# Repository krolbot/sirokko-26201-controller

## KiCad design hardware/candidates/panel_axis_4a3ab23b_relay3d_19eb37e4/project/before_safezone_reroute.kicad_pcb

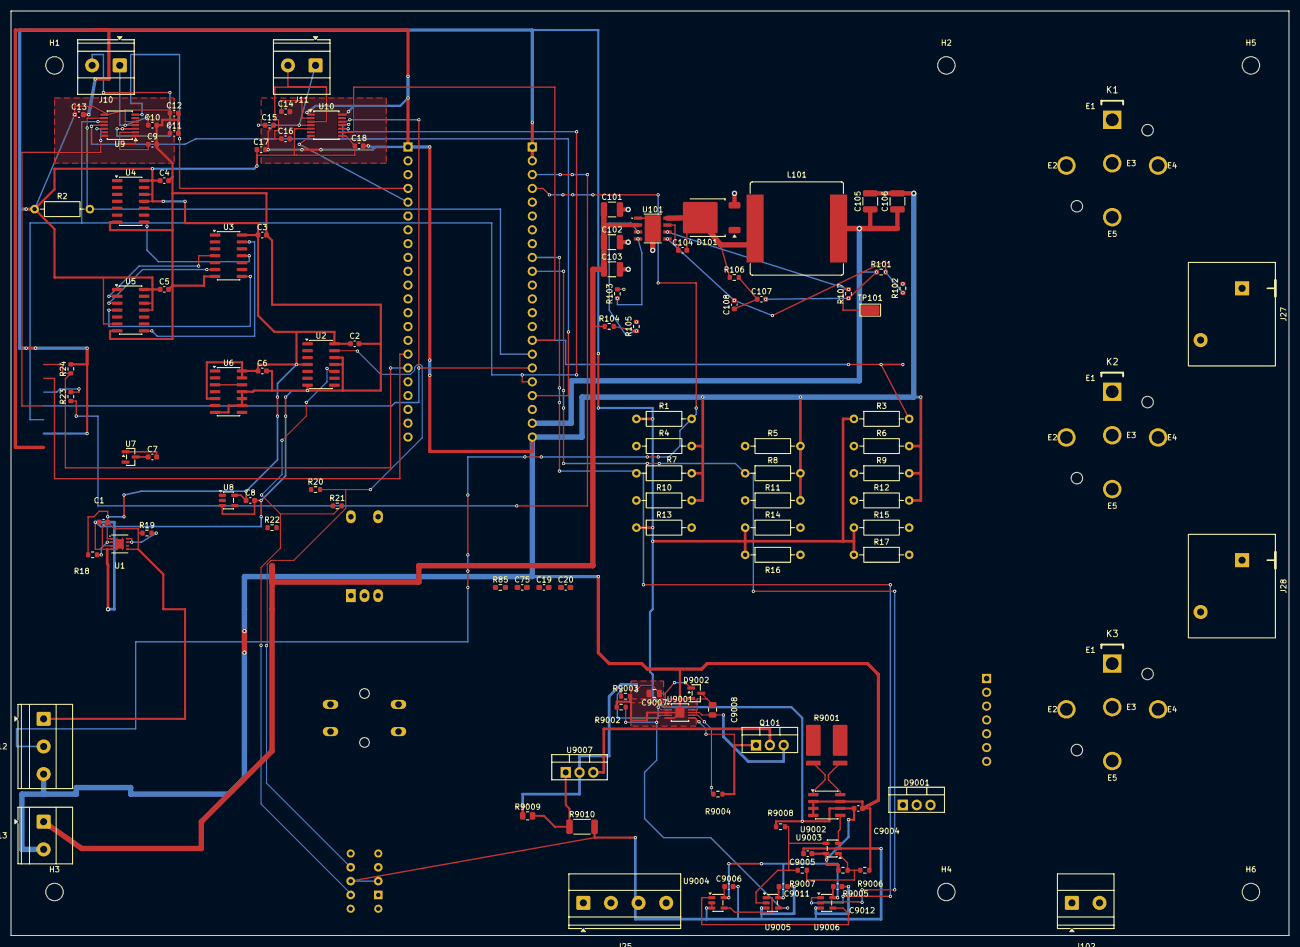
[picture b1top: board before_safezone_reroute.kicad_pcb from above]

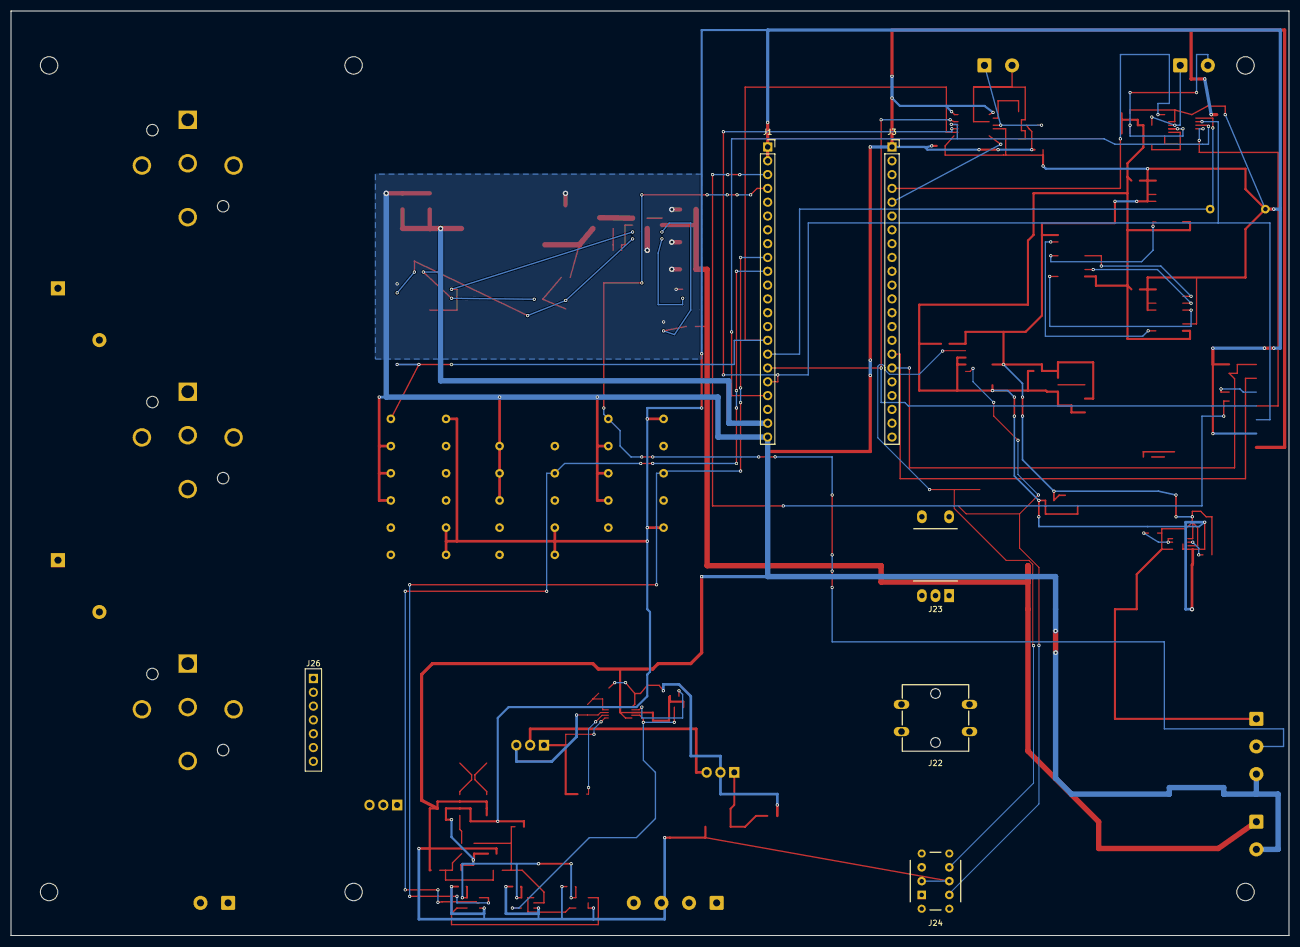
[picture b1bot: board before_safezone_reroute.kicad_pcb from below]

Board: 2 copper layers, 235.0 x 170.0 mm, 125 parts (6 on the bottom side), 76 nets.

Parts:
C1, C2, C3, C4, C5, C6, C7, C8: 100n 16V X7R; C_0603_1608Metric
C9, C14: 0.1uF X7R 16V BIAS; C_0603_1608Metric
C10, C15: 0.01uF X7R 16V T+ filter; C_0603_1608Metric
C11, C16: 0.01uF X7R 16V T- filter; C_0603_1608Metric
C12, C17: 0.1uF X7R 16V AVDD; C_0603_1608Metric
C13, C18: 0.1uF X7R 16V DVDD; C_0603_1608Metric
C19: 10n ENC_A_FILTER; C_0603_1608Metric_Pad1.08x0.95mm_HandSolder
C20: 10n ENC_B_FILTER; C_0603_1608Metric_Pad1.08x0.95mm_HandSolder
C75: 10n; C_0603_1608Metric_Pad1.08x0.95mm_HandSolder
C101, C102: 2.2uF 100V X7R; C_1210_3225Metric
C103: 22uF 100V BULK; C_1210_3225Metric
C104: 2.2nF 50V X7R; C_0603_1608Metric
C105, C106: 47uF 16V X7R; C_1210_3225Metric
C107: 4.7nF 50V C0G; C_0603_1608Metric
C108: 820pF 50V C0G; C_0603_1608Metric
C9004, C9005, C9006: 100nF X7R 16V; C_0603_1608Metric
C9007: 1uF ±10% X7R 50V 0805; LTC7001 VCC local decoupli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; C_0805_2012Metric
C9008: 1uF ±10% X7R 50V 0805 (BST-TS); C_0805_2012Metric
C9011: 100nF X7R 16V 10%; U9005 local bypass; C_0603_1608Metric
C9012: 100nF X7R 16V 10%; U9006 local bypass; C_0603_1608Metric
D101: STPS5H100B-TR; TO-252-2
D9001: STPS30H100CW; common cathode: K/pin2/tab -> MOTOR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; TO-220-3_Vertical
D9002: MMBD1501A; 200V 200mA silicon low-leakage bootstr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; SOT-23
H1, H2, H3, H4: M3; MountingHole_3.2mm_M3
H5, H6: M3 SUPPORT; MountingHole_3.2mm_M3
J1: DEVKITC1_J1; PinSocket_1x22_P2.54mm_Vertical
J3: DEVKITC1_J3; PinSocket_1x22_P2.54mm_Vertical
J10: TC_K_EXHAUST_T+_T-; TerminalBlock_Phoenix_MKDS-1,5-2-5.08_1x02_P5.08mm_Horizont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
J11: TC_K_AIR_T+_T-; TerminalBlock_Phoenix_MKDS-1,5-2-5.08_1x02_P5.08mm_Horizont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
J12: ROOM_DS18B20_HARNESS; TerminalBlock_Phoenix_MKDS-1,5-3-5.08_1x03_P5.08mm_Horizont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
J13: 24V_LOGIC_INPUT_ONLY__DRAFT_NOT_FOR_ORDER; TerminalBlock_Phoenix_MKDS-1,5-2-5.08_1x02_P5.08mm_Horizont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
J22: START_STOP B3F-4055 + B32-1380 RED; SW_SPST_Omron_B3F-40xx
J23: ENCODER EC11E15244G1; RotaryEncoder_Alps_EC11E15244G1
J24: RESET NKK BB25AB-FA; SW_NKK_BB25AB-FA
J25: THERMAL_AND_HW_ENABLE_3V3_ONLY; TerminalBlock_Phoenix_MKDS-1,5-4-5.08_1x04_P5.08mm_Horizont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
J26: TFT_GMT020-02-7P_ST7789V_7P_SOCKET__FOOTPRINT_NOT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; Connfly_DS1023_1x07S21_P2.54mm
J27: GLOW_OUTPUT_PHOENIX_1756993__POWER_PATH_NOT_CONNE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; Phoenix_1756993_MKDS5HV_2_9.52_ZSZS
J28: CLUTCH_OUTPUT_PHOENIX_1756993__POWER_PATH_NOT_CON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; Phoenix_1756993_MKDS5HV_2_9.52_ZSZS
J102: MOTOR_24V_HIGH_SPEED; 125W_HEATER_NAMEPLATE_NOT_M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; TerminalBlock_Phoenix_MKDS-1,5-2-5.08_1x02_P5.08mm_Horizont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
K1, K2, K3: DZ85AB-5-PCB MECH HOLD; DZ85AB_5_PCB_MECHANICAL_PINMAP_HOLD
L101: 33uH Isat>=10A; L_Bourns_SRP1770TA_16.9x16.9mm
Q101: IRFB4110PBF (100V; RDS(on) @ VGS=10V); TO-220-3_Vertical
R1: 4k7; R_Axial_DIN0207_L6.3mm_D2.5mm_P10.16mm_Horizontal
R2, R3, R4, R5, R6, R7, R8, R9, R10, R11, R12, R13, R14, R15: 10k; R_Axial_DIN0207_L6.3mm_D2.5mm_P10.16mm_Horizontal
R16: 2.2k ENC_A_PULLUP; R_Axial_DIN0207_L6.3mm_D2.5mm_P10.16mm_Horizontal
R17: 2.2k ENC_B_PULLUP; R_Axial_DIN0207_L6.3mm_D2.5mm_P10.16mm_Horizontal
R18, R19, R20, R21, R22, R102, R105, R107: 10k 1%; R_0603_1608Metric
R23: 33R TFT_RESET_SERIES; R_0603_1608Metric
R24: 10k TFT_CS_PULLUP; R_0603_1608Metric
R85: 2.2k; R_0603_1608Metric_Pad0.98x0.95mm_HandSolder
R101, R103: 31.6k 1%; R_0603_1608Metric
R104: 100k 1%; R_0603_1608Metric
R106: 82k 1%; R_0603_1608Metric
R9001: WSLP27262L000FEA; 2mOhm 1% 5W @70C; WSLP2726
R9002: 100k 1% gate-command pull-down; R_0603_1608Metric
R9003: 130k 1% (VCCUV ≈9.1V rising); R_0603_1608Metric
R9004: 10R gate turn-on damping; R_0603_1608Metric
R9005: 30.1k 1% OCP threshold high; R_0603_1608Metric
R9006: 10.0k 1% OCP threshold low; R_0603_1608Metric
R9007: 1.00M 1% OCP hysteresis feedback; R_0603_1608Metric
R9008: 10k 1% OCP_OK pull-up; R_0603_1608Metric
R9009: 75R 1% 0.125W; LM317 OUT→ADJ; R_0805_2012Metric
R9010: 681R 1% 0.5W; LM317 ADJ→GND; R_2010_5025Metric
TP101: PGOOD_5V_NOT_GPIO; TestPoint_Keystone_5015_Micro_Mini
U1: TPS3431SDRBR; TPS3431_DRB0008A
U2: SN74HCS74D; SOIC-14_3.9x8.7mm_P1.27mm
U3: SN74HCS14D; SOIC-14_3.9x8.7mm_P1.27mm
U4, U5: SN74HCS30D; SOIC-14_3.9x8.7mm_P1.27mm
U6: SN74HCS11D; SOIC-14_3.9x8.7mm_P1.27mm
U7: TPS3839G33DBZR; SOT-23
U8: SN74LVC1G14DBVR; SOT-23-5
U9, U10: MAX31856MUD+; TSSOP-14_4.4x5mm_P0.65mm
U101: LM5013DDAR; DDA0008B_LM5013DDAR_TI4214849B
U9001: LTC7001IMSE#PBF; MSOP-10 EP; MSOP-10-1EP_3x3mm_P0.5mm_EP1.68x1.88mm
U9002: INA240A1ID; SOIC-8_3.9x4.9mm_P1.27mm
U9003: TLV9020DBVR; SOT-23-5
U9004: SN74LVC1G32DBVR; SOT-23-5
U9005, U9006: SN74LVC1G08DBVR; SOT-23-5
U9007: LM317HVT/NOPB TO-220; TJ 0…125C; TO-220-3_Vertical

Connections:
+5V_DEVKIT: C105.1, C106.1, C107.2, J1.21, L101.2, R101.1, R107.1
/+3V3: C1.1, C2.1, C3.1, C4.1, C5.1, C6.1, C7.1, C8.1, C12.1, C13.1, C17.1, C18.1, C9004.1, C9005.1, C9006.1, C9011.1, C9012.1, J1.1, J1.2, J12.1, J25.1, J26.6, R1.1, R2.1, R3.1, R13.1, R14.1, R15.1, R16.1, R17.1, R18.1, R19.1, R20.1, R21.1, R24.2, R85.1, R9005.1, R9008.1, U1.1, U1.3, U1.5, U2.4, U2.14, U3.14, U4.11, U4.12, U4.14, U5.6, U5.11, U5.12, U5.14, U6.5, U6.13, U6.14, U7.3, U8.5, U9.5, U9.8, U10.5, U10.8, U9002.6, U9003.5, U9004.5, U9005.5, U9006.5
/ALLOW_LATCH: U2.5, U6.1
/ARM_READY: J3.7, R10.1, U4.5, U5.1
/CLEAR_OK: U2.1, U3.10, U6.2
/ENC_A: C19.1, J3.9, J23.1, R16.2
/ENC_B: C20.1, J3.8, J23.3, R17.2
/ENC_SW: C75.1, J3.10, J23.4, R85.2
/EN_CHIP_PU: J1.3, R23.1
/EXT_SAFETY_ENABLE: J25.4, U6.6
/FAN_REQUEST: J1.9, R7.1, U9006.1
/FUEL_CMD: J1.8, R5.1, U3.3
/FUEL_PERMIT: J3.18, R6.1, U3.5, U6.4
/GLOW_CMD: J1.20, R4.1, U3.9
/GND: C1.2, C2.2, C3.2, C4.2, C5.2, C6.2, C7.2, C8.2, C9.2, C10.2, C11.2, C12.2, C13.2, C14.2, C15.2, C16.2, C17.2, C18.2, C19.2, C20.2, C75.2, C101.2, C102.2, C103.2, C105.2, C106.2, C9004.2, C9005.2, C9006.2, C9007.2, C9011.2, C9012.2, D101.3, D9001.1, D9001.3, J1.22, J3.1, J3.21, J3.22, J12.3, J13.2, J22.2, J23.2, J23.5, J24.2, J24.5, J25.3, J26.7, J27.2, J28.2, J102.2, R4.2, R5.2, R6.2, R7.2, R8.2, R9.2, R10.2, R11.2, R12.2, R22.2, R102.2, R103.2, R105.2, R9002.2, R9003.2, R9006.2, R9010.2, U1.4, U1.9, U2.7, U2.11, U2.12, U3.7, U4.7, U5.7, U6.7, U6.9, U6.10, U6.11, U7.1, U8.3, U9.1, U9.14, U10.1, U10.14, U101.1, U101.9, U9001.3, U9001.5, U9001.11, U9002.2, U9002.3, U9002.4, U9002.7, U9003.2, U9004.2, U9004.3, U9005.3, U9006.3
/HW_RESET_CLK: U2.3, U2.9
/LOGIC_POWER_24_TO_5V__DRAFT_NOT_FOR_ORDER/BOOT: C104.1, U101.7
/LOGIC_POWER_24_TO_5V__DRAFT_NOT_FOR_ORDER/EN_LOGIC: R104.2, R105.1, U101.3
/LOGIC_POWER_24_TO_5V__DRAFT_NOT_FOR_ORDER/FB: C108.2, R101.2, R102.1, U101.5
/LOGIC_POWER_24_TO_5V__DRAFT_NOT_FOR_ORDER/PGOOD_5V: R107.2, TP101.1, U101.6
/LOGIC_POWER_24_TO_5V__DRAFT_NOT_FOR_ORDER/RAMP: C107.1, C108.1, R106.2
/LOGIC_POWER_24_TO_5V__DRAFT_NOT_FOR_ORDER/RON: R103.1, U101.4
/LOGIC_POWER_24_TO_5V__DRAFT_NOT_FOR_ORDER/SW: C104.2, D101.2, L101.1, R106.1, U101.8
/MOTOR_PWM_REBUILD_CANDIDATE/BST: C9008.1, D9002.3, U9001.9
/MOTOR_PWM_REBUILD_CANDIDATE/FAN_REQUEST_OR_EMERG: U9004.4, U9005.1
/MOTOR_PWM_REBUILD_CANDIDATE/FAN_WORK_PWM: U9004.1, U9006.4
/MOTOR_PWM_REBUILD_CANDIDATE/GATE_Q101: Q101.1, R9004.2, U9001.6
/MOTOR_PWM_REBUILD_CANDIDATE/ISENSE_OUT: U9002.5, U9003.3
/MOTOR_PWM_REBUILD_CANDIDATE/MOTOR_GATE_CMD: R9002.1, U9001.4, U9005.4
/MOTOR_PWM_REBUILD_CANDIDATE/MOTOR_POS: D9001.2, J102.1, R9001.2, U9002.1
/MOTOR_PWM_REBUILD_CANDIDATE/OCP_OK: R9007.1, R9008.2, U9003.4, U9005.2
/MOTOR_PWM_REBUILD_CANDIDATE/OCP_THRESH: R9005.2, R9006.1, R9007.2, U9003.1
/MOTOR_PWM_REBUILD_CANDIDATE/SW_SHUNT_HI: C9008.2, Q101.3, R9001.1, U9001.8, U9002.8
/MOTOR_PWM_REBUILD_CANDIDATE/TGUP: R9004.1, U9001.7
/MOTOR_PWM_REBUILD_CANDIDATE/VADJ: R9009.2, R9010.1, U9007.1
/MOTOR_PWM_REBUILD_CANDIDATE/VCCUV: R9003.1, U9001.2
/MOTOR_PWM_REBUILD_CANDIDATE/VDRV12V: C9007.1, D9002.1, R9009.1, U9001.1, U9007.2
/NOT_CLEAR_OK: U3.11, U4.8
/NOT_FUEL_CMD: U3.4, U5.2
/NOT_FUEL_PERMIT: U3.6, U5.3
/NOT_GLOW_CMD: U3.8, U5.4
/NOT_RESET_ACCEPT: U3.13, U5.8
/NOT_SW_TRIP: U3.2, U4.6
/P24_PROTECTED: C101.1, C102.1, C103.1, J13.1, Q101.2, R104.1, U101.2, U9007.3
/PG_OK: U4.1, U7.2
/RESET_ACCEPT: U2.2, U3.12
/RESET_HW_NC_N: J24.6, R20.2, U2.13
/RESET_HW_NO_N: J24.4, R21.2, U2.10
/RESET_REQUEST: J1.6, J24.1, R13.2
/ROOM_DQ: J1.4, J12.2, R1.2
/SAFETY_OK: J1.5, R12.1, U6.3, U6.12
/SPEED_CMD: J1.10, R8.1, U9006.2
/START_REQUEST: J1.7, J22.1, R14.2, U5.5
/STOP_OK: U4.3, U8.4
/STOP_STATUS: J1.12, R15.2, U8.2
/SW_TRIP: J3.6, R11.1, U3.1
/TC_AIR_BIAS: C14.1, U10.2
/TC_AIR_CS: J1.15, R3.2, U10.9
/TC_AIR_DRDY: J3.5, U10.7
/TC_AIR_TM: C16.1, J11.2, U10.3
/TC_AIR_TP: C15.1, J11.1, U10.4
/TC_EXH_BIAS: C9.1, U9.2
/TC_EXH_CS: J1.16, R2.2, U9.9
/TC_EXH_DRDY: J3.4, U9.7
/TC_EXH_TM: C11.1, J10.2, U9.3
/TC_EXH_TP: C10.1, J10.1, U9.4
/TC_SCK: J1.18, J26.5, U9.10, U10.10
/TC_SDI_MOSI: J1.17, J26.4, U9.12, U10.12
/TC_SDO_MISO: J1.19, U9.11, U10.11
/TFT_CS: J3.17, J26.1, R24.1
/TFT_DC: J3.16, J26.2
/TFT_RESET_N: J26.3, R23.2
/THERMAL_OK: J25.2, R22.1, U4.4
/WD_CWD_FIXED: R18.2, U1.2
/WD_HEARTBEAT: J1.11, R9.1, U1.6
/WD_OK: R19.2, U1.7, U1.8, U4.2

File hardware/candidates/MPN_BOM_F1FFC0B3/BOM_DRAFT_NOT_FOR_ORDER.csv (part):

"Ref","Value","Footprint","Qty","DNP","MPN","Manufacturer","Datasheet"
"C1","100n 16V X7R","Capacitor_SMD:C_0603_1608Metric","1","","","",""
"C2","100n 16V X7R","Capacitor_SMD:C_0603_1608Metric","1","","","",""
"C3","100n 16V X7R","Capacitor_SMD:C_0603_1608Metric","1","","","",""
"C4","100n 16V X7R","Capacitor_SMD:C_0603_1608Metric","1","","","",""
"C5","100n 16V X7R","Capacitor_SMD:C_0603_1608Metric","1","","","",""
"C6","100n 16V X7R","Capacitor_SMD:C_0603_1608Metric","1","","","",""
"C7","100n 16V X7R","Capacitor_SMD:C_0603_1608Metric","1","","","",""
"C8","100n 16V X7R","Capacitor_SMD:C_0603_1608Metric","1","","","",""
"C9","0.1uF X7R 16V BIAS","Capacitor_SMD:C_0603_1608Metric","1","","","",""
"C10","0.01uF X7R 16V T+ filter","Capacitor_SMD:C_0603_1608Metric","1","","","",""
"C11","0.01uF X7R 16V T- filter","Capacitor_SMD:C_0603_1608Metric","1","","","",""
"C12","0.1uF X7R 16V AVDD","Capacitor_SMD:C_0603_1608Metric","1","","","",""
"C13","0.1uF X7R 16V DVDD","Capacitor_SMD:C_0603_1608Metric","1","","","",""
"C14","0.1uF X7R 16V BIAS","Capacitor_SMD:C_0603_1608Metric","1","","","",""
"C15","0.01uF X7R 16V T+ filter","Capacitor_SMD:C_0603_1608Metric","1","","","",""
"C16","0.01uF X7R 16V T- filter","Capacitor_SMD:C_0603_1608Metric","1","","","",""
"C17","0.1uF X7R 16V AVDD","Capacitor_SMD:C_0603_1608Metric","1","","","",""
"C18","0.1uF X7R 16V DVDD","Capacitor_SMD:C_0603_1608Metric","1","","","",""
"C19","10n ENC_A_FILTER","Capacitor_SMD:C_0603_1608Metric_Pad1.08x0.95mm_HandSolder","1","","","",""
"C20","10n ENC_B_FILTER","Capacitor_SMD:C_0603_1608Metric_Pad1.08x0.95mm_HandSolder","1","","","",""
"C75","10n","Capacitor_SMD:C_0603_1608Metric_Pad1.08x0.95mm_HandSolder","1","","","",""
"C101","2.2uF 100V X7R","Capacitor_SMD:C_1210_3225Metric","1","","GRM32ER72A225KA35L","",""
"C102","2.2uF 100V X7R","Capacitor_SMD:C_1210_3225Metric","1","","GRM32ER72A225KA35L","",""
"C103","22uF 100V BULK","Capacitor_SMD:C_1210_3225Metric","1","","GRM32ER72A226KE20L","",""
"C104","2.2nF 50V X7R","Capacitor_SMD:C_0603_1608Metric","1","","CC0603KRX7R9BB222","",""
"C105","47uF 16V X7R","Capacitor_SMD:C_1210_3225Metric","1","","GRM32ER61C476KE15L","",""
"C106","47uF 16V X7R","Capacitor_SMD:C_1210_3225Metric","1","","GRM32ER61C476KE15L","",""
"C107","4.7nF 50V C0G","Capacitor_SMD:C_0603_1608Metric","1","","GRM1885C1H472JA01D","",""
"C108","820pF 50V C0G","Capacitor_SMD:C_0603_1608Metric","1","","CC0603JRNPO9BN821","",""
"C301","10uF GRM21BR61E106KA73L","Sirokko_TFT_Passives:C_Murata_GRM21B_2012_Reflow","1","","","",""
"C302","10uF GRM21BR61E106KA73L","Sirokko_TFT_Passives:C_Murata_GRM21B_2012_Reflow","1","","","",""
"C303","100nF GRM188R71E104KA01D","Sirokko_TFT_Passives:C_Murata_GRM188_1608_Reflow","1","","","",""
"C304","47uF GRM32ER61C476KE15L","Sirokko_TFT_Passives:C_Murata_GRM32E_3225_Reflow","1","","","",""
"C305","100nF","Capacitor_SMD:C_0603_1608Metric","1","","","",""
"C306","100nF","Capacitor_SMD:C_0603_1608Metric","1","","","",""
"C9004","100nF X7R 16V","Capacitor_SMD:C_0603_1608Metric","1","","","",""
"C9005","100nF X7R 16V","Capacitor_SMD:C_0603_1608Metric","1","","","",""
"C9006","100nF X7R 16V","Capacitor_SMD:C_0603_1608Metric","1","","","",""
"C9007","1uF ±10% X7R 50V 0805; LTC7001 VCC local decoupling","Capacitor_SMD:C_0805_2012Metric","1","","GRM21BR71H105KA12L","",""
"C9008","1uF ±10% X7R 50V 0805 (BST-TS)","Capacitor_SMD:C_0805_2012Metric","1","","GRM21BR71H105KA12L","",""
"C9011","100nF X7R 16V 10%; U9005 local bypass","Capacitor_SMD:C_0603_1608Metric","1","","","",""
"C9012","100nF X7R 16V 10%; U9006 local bypass","Capacitor_SMD:C_0603_1608Metric","1","","","",""
"D101","STPS5H100B-TR","","1","","STPS5H100B-TR","",""
"D9001","STPS30H100CW; common cathode: K/pin2/tab -> MOTOR_POS; A1/pin1 + A2/pin3 -> GND","Package_TO_SOT_THT:TO-220-3_Vertical","1","","STPS30H100CW","","https://www.st.com/resource/en/datasheet/stps30h100c.pdf"
"D9002","MMBD1501A; 200V 200mA silicon low-leakage bootstrap diode","Package_TO_SOT_SMD:SOT-23","1","","MMBD1501A","ON Semiconductor / Fairchild",""
"J1","DEVKITC1_J1","Connector_PinSocket_2.54mm:PinSocket_1x22_P2.54mm_Vertical","1","","","",""
"J3","DEVKITC1_J3","Connector_PinSocket_2.54mm:PinSocket_1x22_P2.54mm_Vertical","1","","","",""
"J10","TC_K_EXHAUST_T+_T-","TerminalBlock_Phoenix:TerminalBlock_Phoenix_MKDS-1,5-2-5.08_1x02_P5.08mm_Horizontal","1","","","",""
"J11","TC_K_AIR_T+_T-","TerminalBlock_Phoenix:TerminalBlock_Phoenix_MKDS-1,5-2-5.08_1x02_P5.08mm_Horizontal","1","","","",""
"J12","ROOM_DS18B20_HARNESS","TerminalBlock_Phoenix:TerminalBlock_Phoenix_MKDS-1,5-3-5.08_1x03_P5.08mm_Horizontal","1","","1715734","Phoenix Contact","https://static.chipdip.ru/lib/723/DOC011723280.pdf"
"J13","24V_LOGIC_INPUT_ONLY__DRAFT_NOT_FOR_ORDER","TerminalBlock_Phoenix:TerminalBlock_Phoenix_MKDS-1,5-2-5.08_1x02_P5.08mm_Horizontal","1","","1715721","Phoenix Contact","https://static.chipdip.ru/lib/509/DOC040509545.pdf"
"J22","START_STOP B3F-4055 + B32-1380 RED","Button_Switch_THT:SW_SPST_Omron_B3F-40xx","1","","","",""
"J23","ENCODER EC11E15244G1","Sirokko_Panel:RotaryEncoder_Alps_EC11E15244G1","1","","","",""
"J24","RESET NKK BB25AB-FA","Sirokko_Panel:SW_NKK_BB25AB-FA","1","","","",""
"J25","THERMAL_AND_HW_ENABLE_3V3_ONLY","TerminalBlock_Phoenix:TerminalBlock_Phoenix_MKDS-1,5-4-5.08_1x04_P5.08mm_Horizontal","1","","","",""
"J26","TFT_WAVESHARE_18366_CABLE_8P","Sirokko_Connectors:Connfly_DS1021_1x08_P2.54mm_Type1_Drill1.02","1","","DS1021-1*8SF11-B","Connfly",""
"J27","GLOW_OUTPUT_PHOENIX_1756993__POWER_PATH_NOT_CONNECTED","Sirokko_Power:Phoenix_1756993_MKDS5HV_2_9.52_ZSZS","1","","1756993","",""
"J28","CLUTCH_OUTPUT_PHOENIX_1756993__POWER_PATH_NOT_CONNECTED","Sirokko_Power:Phoenix_1756993_MKDS5HV_2_9.52_ZSZS","1","","1756993","",""
"J102","MOTOR_24V_HIGH_SPEED; 125W_HEATER_NAMEPLATE_NOT_MOTOR_RATING","TerminalBlock_Phoenix:TerminalBlock_Phoenix_MKDS-1,5-2-5.08_1x02_P5.08mm_Horizontal","1","","","",""
"L101","33uH Isat>=10A","Inductor_SMD:L_Bourns_SRP1770TA_16.9x16.9mm","1","","SRP1770TA-330M","",""
"L301","744025003 3.3uH","Sirokko_TFT_Passives:L_Wuerth_744025003_2828_Reflow","1","","","",""
"Q101","IRFB4110PBF (100V; RDS(on) @ VGS=10V)","Package_TO_SOT_THT:TO-220-3_Vertical","1","","","",""
"R1","4k7","Resistor_THT:R_Axial_DIN0207_L6.3mm_D2.5mm_P10.16mm_Horizontal","1","","","",""
"R2","10k","Resistor_THT:R_Axial_DIN0207_L6.3mm_D2.5mm_P10.16mm_Horizontal","1","","","",""
"R3","10k","Resistor_THT:R_Axial_DIN0207_L6.3mm_D2.5mm_P10.16mm_Horizontal","1","","","",""
"R4","10k","Resistor_THT:R_Axial_DIN0207_L6.3mm_D2.5mm_P10.16mm_Horizontal","1","","","",""
"R5","10k","Resistor_THT:R_Axial_DIN0207_L6.3mm_D2.5mm_P10.16mm_Horizontal","1","","","",""
"R6","10k","Resistor_THT:R_Axial_DIN0207_L6.3mm_D2.5mm_P10.16mm_Horizontal","1","","","",""
"R7","10k","Resistor_THT:R_Axial_DIN0207_L6.3mm_D2.5mm_P10.16mm_Horizontal","1","","","",""
"R8","10k","Resistor_THT:R_Axial_DIN0207_L6.3mm_D2.5mm_P10.16mm_Horizontal","1","","","",""
"R9","10k","Resistor_THT:R_Axial_DIN0207_L6.3mm_D2.5mm_P10.16mm_Horizontal","1","","","",""
"R10","10k","Resistor_THT:R_Axial_DIN0207_L6.3mm_D2.5mm_P10.16mm_Horizontal","1","","","",""
"R11","10k","Resistor_THT:R_Axial_DIN0207_L6.3mm_D2.5mm_P10.16mm_Horizontal","1","","","",""
"R12","10k","Resistor_THT:R_Axial_DIN0207_L6.3mm_D2.5mm_P10.16mm_Horizontal","1","","","",""
"R13","10k","Resistor_THT:R_Axial_DIN0207_L6.3mm_D2.5mm_P10.16mm_Horizontal","1","","","",""
"R14","10k","Resistor_THT:R_Axial_DIN0207_L6.3mm_D2.5mm_P10.16mm_Horizontal","1","","","",""
"R15","10k","Resistor_THT:R_Axial_DIN0207_L6.3mm_D2.5mm_P10.16mm_Horizontal","1","","","",""
"R16","2.2k ENC_A_PULLUP","Resistor_THT:R_Axial_DIN0207_L6.3mm_D2.5mm_P10.16mm_Horizontal","1","","","",""
"R17","2.2k ENC_B_PULLUP","Resistor_THT:R_Axial_DIN0207_L6.3mm_D2.5mm_P10.16mm_Horizontal","1","","","",""
"R18","10k 1%","Resistor_SMD:R_0603_1608Metric","1","","","",""
"R19","10k 1%","Resistor_SMD:R_0603_1608Metric","1","","","",""
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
